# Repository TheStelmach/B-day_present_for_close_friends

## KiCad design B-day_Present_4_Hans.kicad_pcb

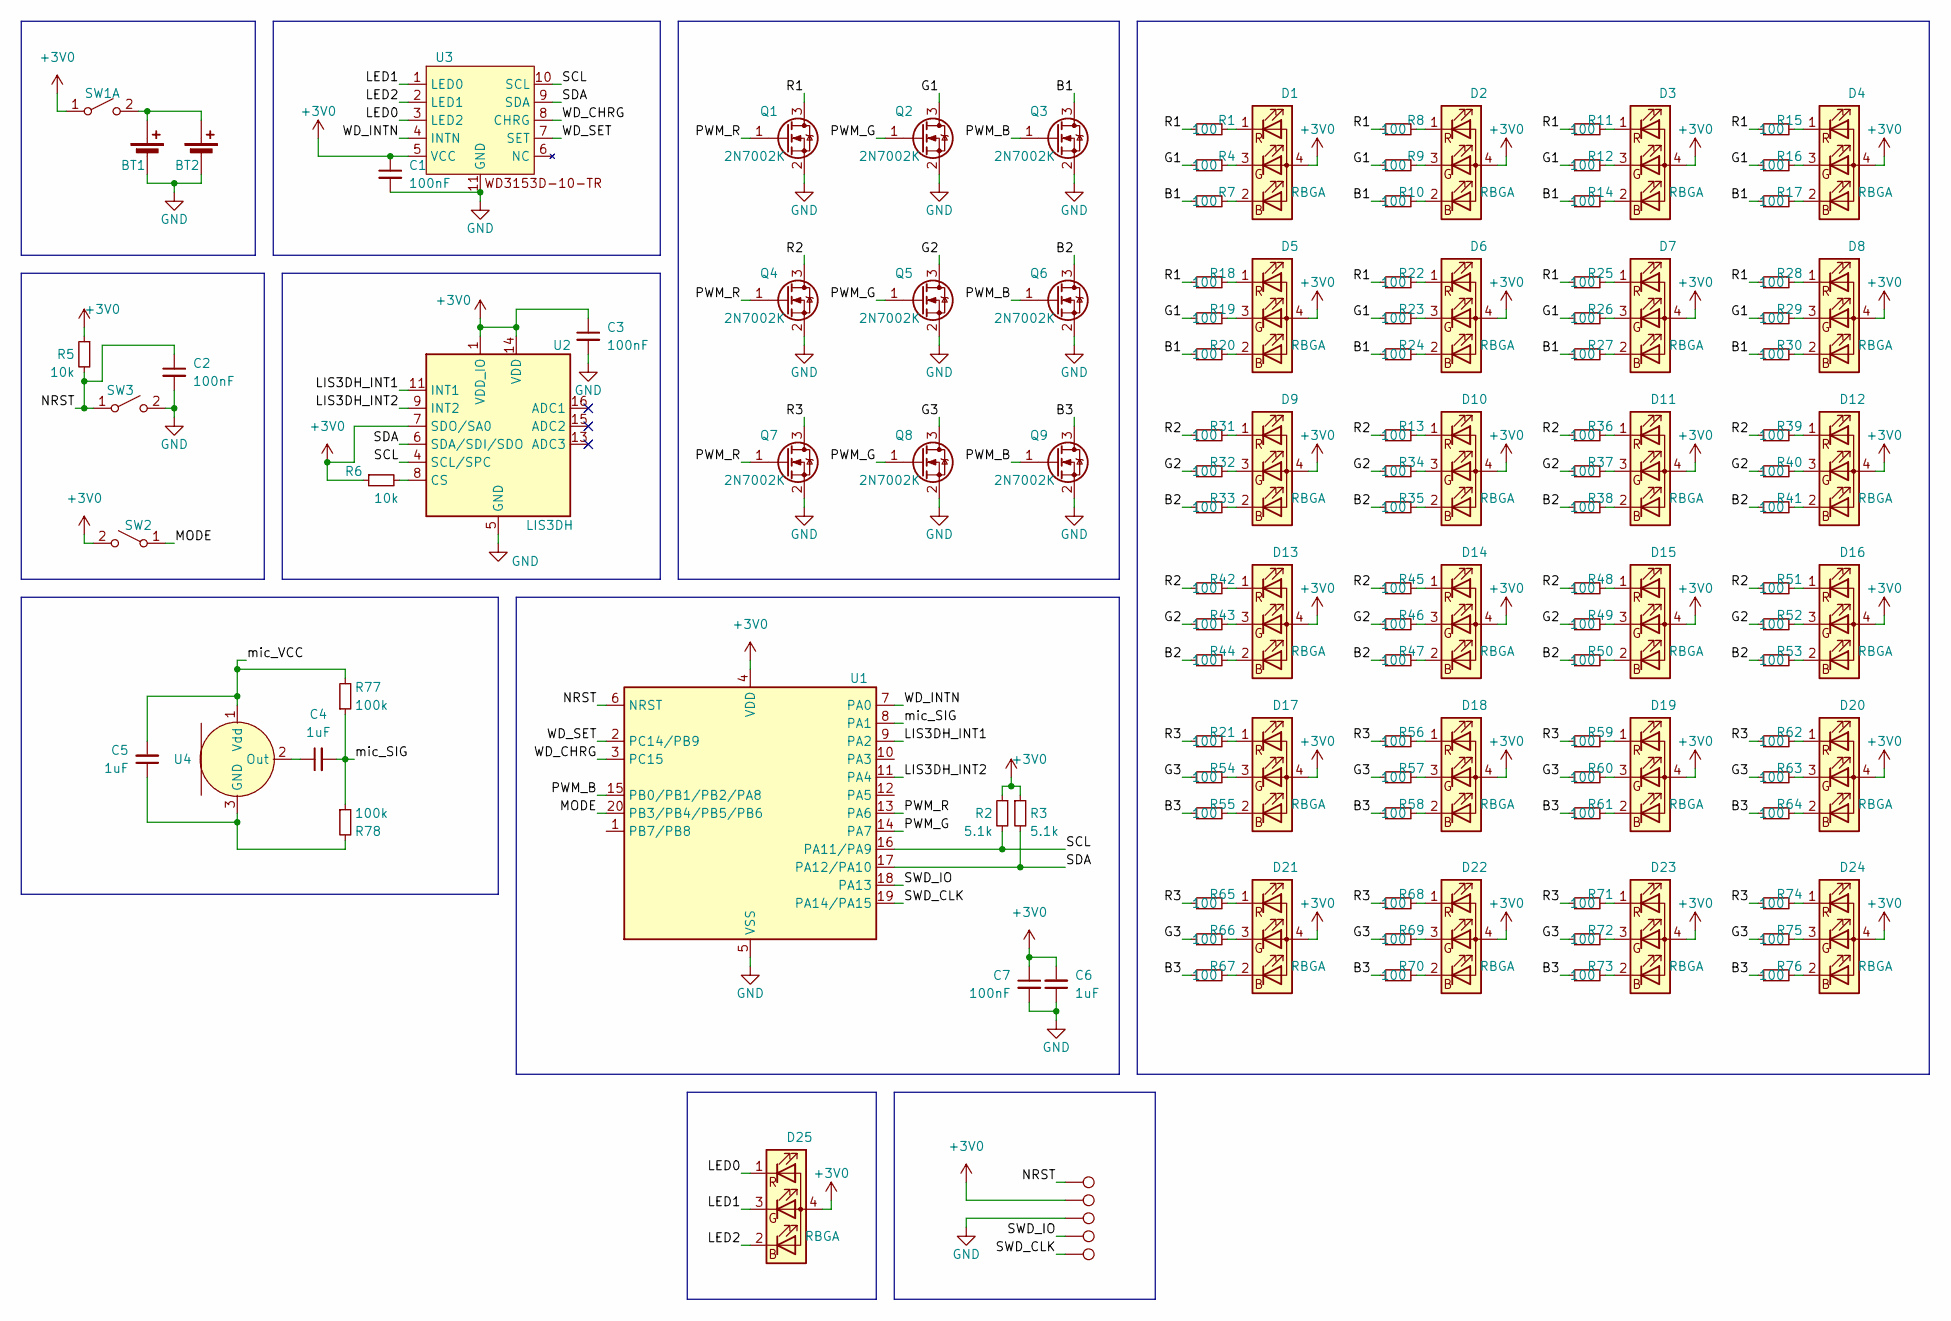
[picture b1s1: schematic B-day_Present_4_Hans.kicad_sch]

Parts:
BT1, BT2: Battery_Cell; BatteryHolder_Keystone_1058_1x2032
C1, C2, C3, C7: 100nF; C_0603_1608Metric_Pad1.08x0.95mm_HandSolder
C4, C5, C6: 1uF; C_0805_2012Metric_Pad1.18x1.45mm_HandSolder
D1, D2, D3, D4, D5, D6, D7, D8, D9, D10, D11, D12, D13, D14, D15, D16, D17, D18, D19, D20, D21, D22, D23, D24, D25: RBGA; LED_RGB_0606_NH-B1515RGBA-HF
Q1, Q2, Q3, Q4, Q5, Q6, Q7, Q8, Q9: 2N7002K; SOT-23
R1, R4, R7, R8, R9, R10, R11, R12, R13, R14, R15, R16, R17, R18, R19, R20, R21, R22, R23, R24, R25, R26, R27, R28, R29, R30, R31, R32, R33, R34, R35, R36, R37, R38, R39, R40, R41, R42, R43, R44, R45, R46, R47, R48, R49, R50, R51, R52, R53, R54, R55, R56, R57, R58, R59, R60, R61, R62, R63, R64, R65, R66, R67, R68, R69, R70, R71, R72, R73, R74, R75, R76: 100; R_0603_1608Metric_Pad0.98x0.95mm_HandSolder
R2, R3: 5.1k; R_0603_1608Metric_Pad0.98x0.95mm_HandSolder
R5, R6: 10k; R_0603_1608Metric_Pad0.98x0.95mm_HandSolder
R77, R78: 100k; R_0603_1608Metric_Pad0.98x0.95mm_HandSolder
SW1: SW_DPST_x2; SW_SPDT_PCM12
SW2, SW3: SW_SPST; SW_SPST_TL3342
TP1, TP2, TP3, TP4, TP5: TestPoint; TestPoint_Pad_D2.0mm
U1: STM32G030F6Px; TSSOP-20_4.4x6.5mm_P0.65mm
U2: LIS3DH; LGA-16_3x3mm_P0.5mm_LayoutBorder3x5y
U3: DFN2x2-10L_WD3153
U4: ANT_3P,1.85x2.75mm_LMA2718B381-OA5-2

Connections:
+3V0: C1.1, C3.1, C6.2, C7.1, D1.4 (A), D2.4 (A), D3.4 (A), D4.4 (A), D5.4 (A), D6.4 (A), D7.4 (A), D8.4 (A), D9.4 (A), D10.4 (A), D11.4 (A), D12.4 (A), D13.4 (A), D14.4 (A), D15.4 (A), D16.4 (A), D17.4 (A), D18.4 (A), D19.4 (A), D20.4 (A), D21.4 (A), D22.4 (A), D23.4 (A), D24.4 (A), D25.4 (A), R2.1, R3.1, R5.1, R6.1, SW1.1 (A), SW2.2 (B), TP4.1, U1.4 (VDD), U2.1 (VDD_IO), U2.7 (SDO/SA0), U2.14 (VDD), U3.5 (VCC)
/B1: Q3.3 (D), R7.1, R10.1, R14.1, R17.1, R20.1, R24.1, R27.1, R30.1
/B2: Q6.3 (D), R33.1, R35.1, R38.1, R41.1, R44.1, R47.1, R50.1, R53.1
/B3: Q9.3 (D), R55.1, R58.1, R61.1, R64.1, R67.1, R70.1, R73.1, R76.1
/G1: Q2.3 (D), R4.1, R9.1, R12.1, R16.1, R19.1, R23.1, R26.1, R29.1
/G2: Q5.3 (D), R32.1, R34.1, R37.1, R40.1, R43.1, R46.1, R49.1, R52.1
/G3: Q8.3 (D), R54.1, R57.1, R60.1, R63.1, R66.1, R69.1, R72.1, R75.1
/LED0: D25.1 (RK), U3.3 (LED2)
/LED1: D25.3 (GK), U3.1 (LED0)
/LED2: D25.2 (BK), U3.2 (LED1)
/LIS3DH_INT1: U1.9 (PA2), U2.11 (INT1)
/LIS3DH_INT2: U1.11 (PA4), U2.9 (INT2)
/MODE: SW2.1 (A), U1.20 (PB3/PB4/PB5/PB6)
/NRST: C2.1, R5.2, SW3.1 (A), TP5.1, U1.6 (NRST)
/PWM_B: Q3.1 (G), Q6.1 (G), Q9.1 (G), U1.15 (PB0/PB1/PB2/PA8)
/PWM_G: Q2.1 (G), Q5.1 (G), Q8.1 (G), U1.14 (PA7)
/PWM_R: Q1.1 (G), Q4.1 (G), Q7.1 (G), U1.13 (PA6)
/R1: Q1.3 (D), R1.1, R8.1, R11.1, R15.1, R18.1, R22.1, R25.1, R28.1
/R2: Q4.3 (D), R13.1, R31.1, R36.1, R39.1, R42.1, R45.1, R48.1, R51.1
/R3: Q7.3 (D), R21.1, R56.1, R59.1, R62.1, R65.1, R68.1, R71.1, R74.1
/SCL: R2.2, U1.16 (PA11/PA9), U2.4 (SCL/SPC), U3.10 (SCL)
/SDA: R3.2, U1.17 (PA12/PA10), U2.6 (SDA/SDI/SDO), U3.9 (SDA)
/SWD_CLK: TP1.1, U1.19 (PA14/PA15)
/SWD_IO: TP2.1, U1.18 (PA13)
/WD_CHRG: U1.3 (PC15), U3.8 (CHRG)
/WD_INTN: U1.7 (PA0), U3.4 (INTN)
/WD_SET: U1.2 (PC14/PB9), U3.7 (SET)
/mic_SIG: C4.2, R77.1, R78.1, U1.8 (PA1)
/mic_VCC: C5.2, R77.2, U4.1 (Vdd)
GND: BT1.2 (-), BT2.2 (-), C1.2, C2.2, C3.2, C6.1, C7.2, Q1.2 (S), Q2.2 (S), Q3.2 (S), Q4.2 (S), Q5.2 (S), Q6.2 (S), Q7.2 (S), Q8.2 (S), Q9.2 (S), SW3.2 (B), TP3.1, U1.5 (VSS), U2.5 (GND), U2.10 (GND), U2.12 (GND), U3.11 (GND)
unnamed: BT1.1 (+), BT2.1 (+), SW1.2 (B)
unnamed: D1.2 (BK), R7.2
unnamed: D1.3 (GK), R4.2
unnamed: D1.1 (RK), R1.2
unnamed: D2.2 (BK), R10.2
unnamed: D2.3 (GK), R9.2
unnamed: D2.1 (RK), R8.2
unnamed: D3.2 (BK), R14.2
unnamed: D3.3 (GK), R12.2
unnamed: D3.1 (RK), R11.2
unnamed: D4.2 (BK), R17.2
unnamed: D4.3 (GK), R16.2
unnamed: D4.1 (RK), R15.2
unnamed: D5.2 (BK), R20.2
unnamed: D5.3 (GK), R19.2
unnamed: D5.1 (RK), R18.2
unnamed: D6.2 (BK), R24.2
unnamed: D6.3 (GK), R23.2
unnamed: D6.1 (RK), R22.2
unnamed: D7.2 (BK), R27.2
unnamed: D7.3 (GK), R26.2
unnamed: D7.1 (RK), R25.2
unnamed: D8.2 (BK), R30.2
unnamed: D8.3 (GK), R29.2
unnamed: D8.1 (RK), R28.2
unnamed: D9.2 (BK), R33.2
unnamed: D9.3 (GK), R32.2
unnamed: D9.1 (RK), R31.2
unnamed: D10.2 (BK), R35.2
unnamed: D10.3 (GK), R34.2
unnamed: D10.1 (RK), R13.2
unnamed: D11.2 (BK), R38.2
unnamed: D11.3 (GK), R37.2
unnamed: D11.1 (RK), R36.2
unnamed: D12.2 (BK), R41.2
unnamed: D12.3 (GK), R40.2
unnamed: D12.1 (RK), R39.2
unnamed: D13.2 (BK), R44.2
unnamed: D13.3 (GK), R43.2
unnamed: D13.1 (RK), R42.2
unnamed: D14.2 (BK), R47.2
unnamed: D14.3 (GK), R46.2
unnamed: D14.1 (RK), R45.2
unnamed: D15.2 (BK), R50.2
unnamed: D15.3 (GK), R49.2
unnamed: D15.1 (RK), R48.2
unnamed: D16.2 (BK), R53.2
unnamed: D16.3 (GK), R52.2
unnamed: D16.1 (RK), R51.2
unnamed: D17.2 (BK), R55.2
unnamed: D17.3 (GK), R54.2
unnamed: D17.1 (RK), R21.2
unnamed: D18.2 (BK), R58.2
unnamed: D18.3 (GK), R57.2
unnamed: D18.1 (RK), R56.2
unnamed: D19.2 (BK), R61.2
unnamed: D19.3 (GK), R60.2
unnamed: D19.1 (RK), R59.2
unnamed: D20.2 (BK), R64.2
unnamed: D20.3 (GK), R63.2
unnamed: D20.1 (RK), R62.2
unnamed: D21.2 (BK), R67.2
unnamed: D21.3 (GK), R66.2
unnamed: D21.1 (RK), R65.2
unnamed: D22.2 (BK), R70.2
unnamed: D22.3 (GK), R69.2
unnamed: D22.1 (RK), R68.2
unnamed: D23.2 (BK), R73.2
unnamed: D23.3 (GK), R72.2
unnamed: D23.1 (RK), R71.2
unnamed: D24.2 (BK), R76.2
unnamed: D24.3 (GK), R75.2
unnamed: D24.1 (RK), R74.2
unnamed: R6.2, U2.8 (CS)
unnamed: C5.1, R78.2, U4.3 (GND)
unnamed: C4.1, U4.2 (Out)

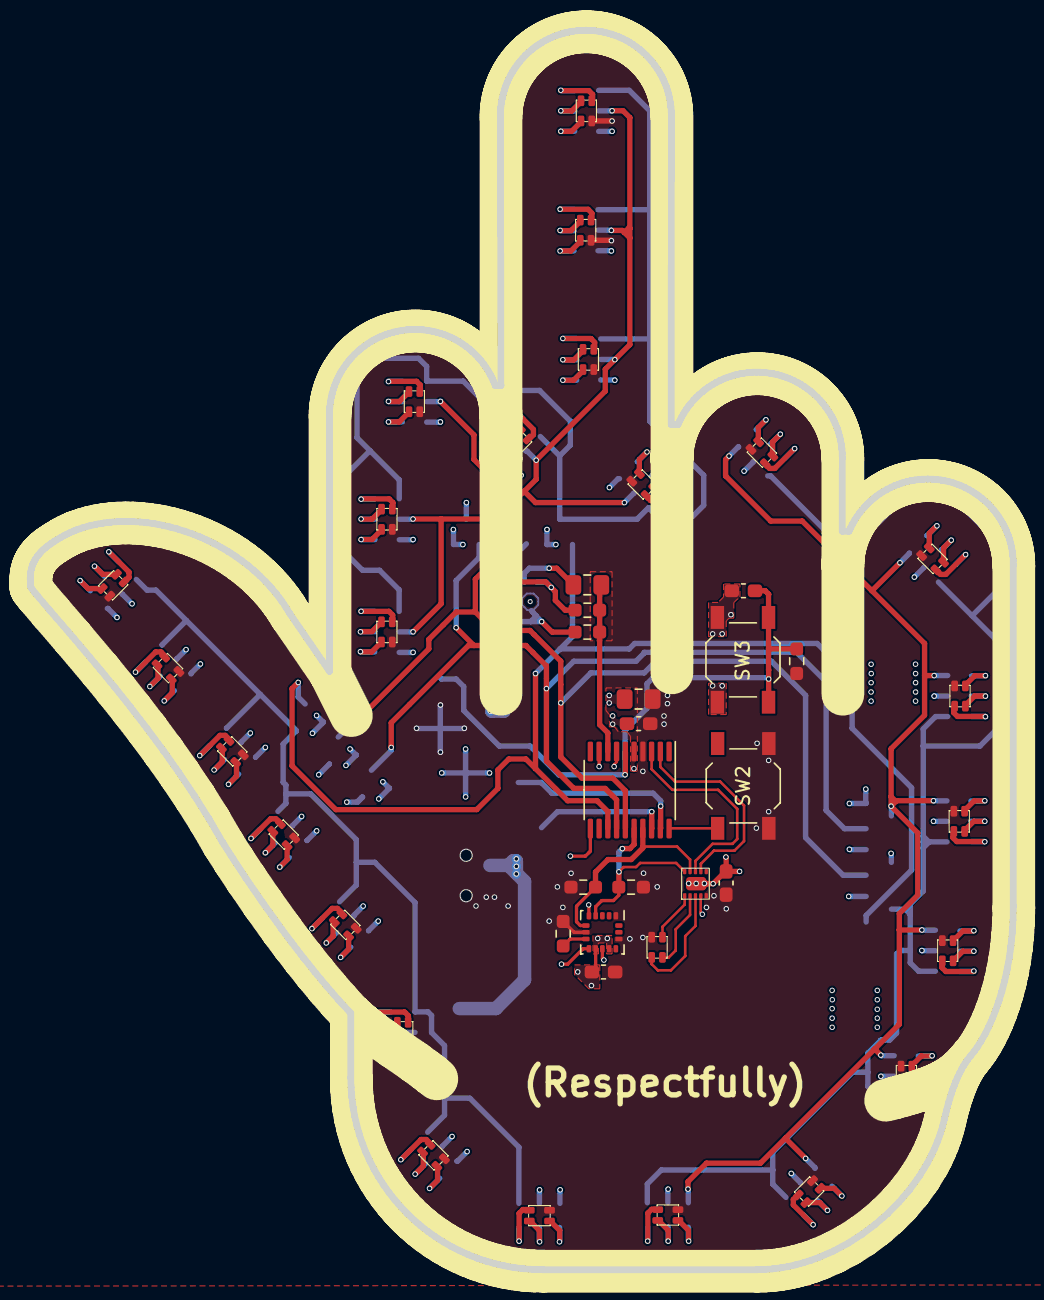
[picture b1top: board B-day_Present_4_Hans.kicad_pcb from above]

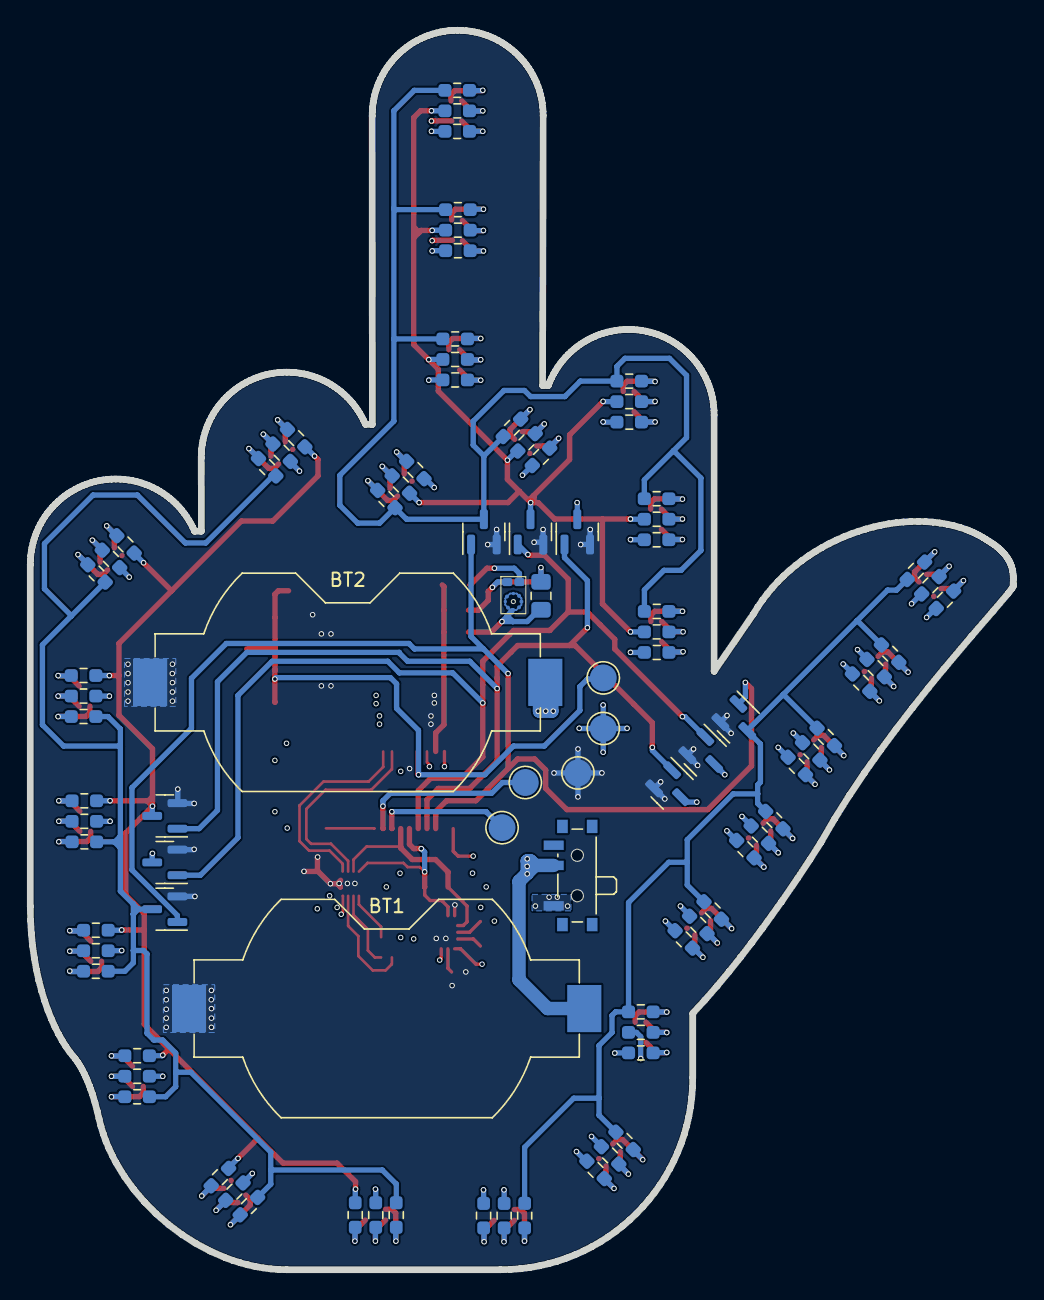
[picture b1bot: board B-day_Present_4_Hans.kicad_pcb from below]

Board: 4 copper layers, 73.0 x 92.1 mm, 133 parts (91 on the bottom side), 106 nets.
